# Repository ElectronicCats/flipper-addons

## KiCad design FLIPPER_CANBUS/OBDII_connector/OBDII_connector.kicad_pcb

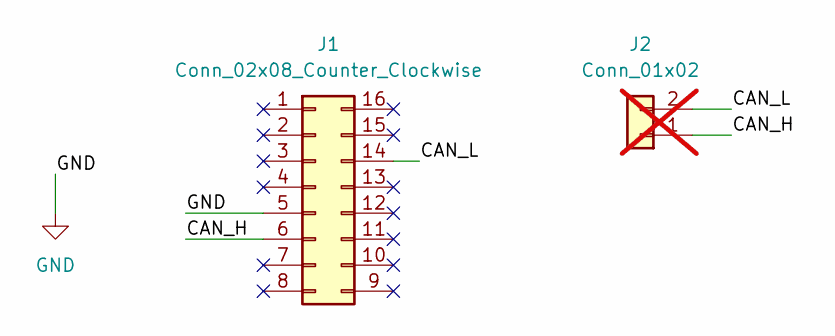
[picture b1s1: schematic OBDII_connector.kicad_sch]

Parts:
J1: Conn_02x08_Counter_Clockwise; OBD-II-Sparkfun v2.0
J2: Conn_01x02; PinHeader_1x02_P2.54mm_Vertical; not fitted

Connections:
/CAN_H: J1.6, J2.1
/CAN_L: J1.14, J2.2
GND: J1.5

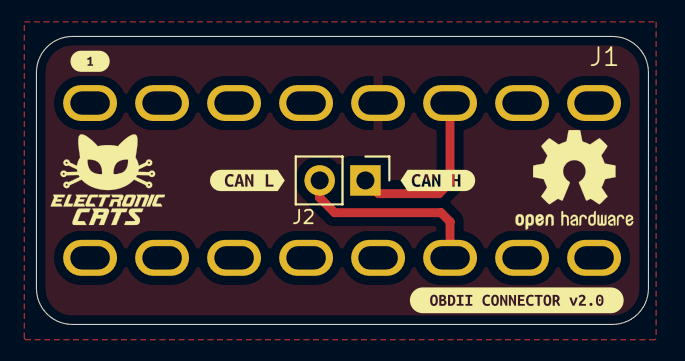
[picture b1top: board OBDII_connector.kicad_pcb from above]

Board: 2 copper layers, 34.0 x 16.0 mm, 6 parts (0 on the bottom side), 2 nets.

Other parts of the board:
kibuzzard-66AA65D6: G***; kibuzzard-66AA65D6
kibuzzard-66AA65F0: G***; kibuzzard-66AA65F0
kibuzzard-6646749E: G***; kibuzzard-6646749E
kibuzzard-66467618: G***; kibuzzard-66467618

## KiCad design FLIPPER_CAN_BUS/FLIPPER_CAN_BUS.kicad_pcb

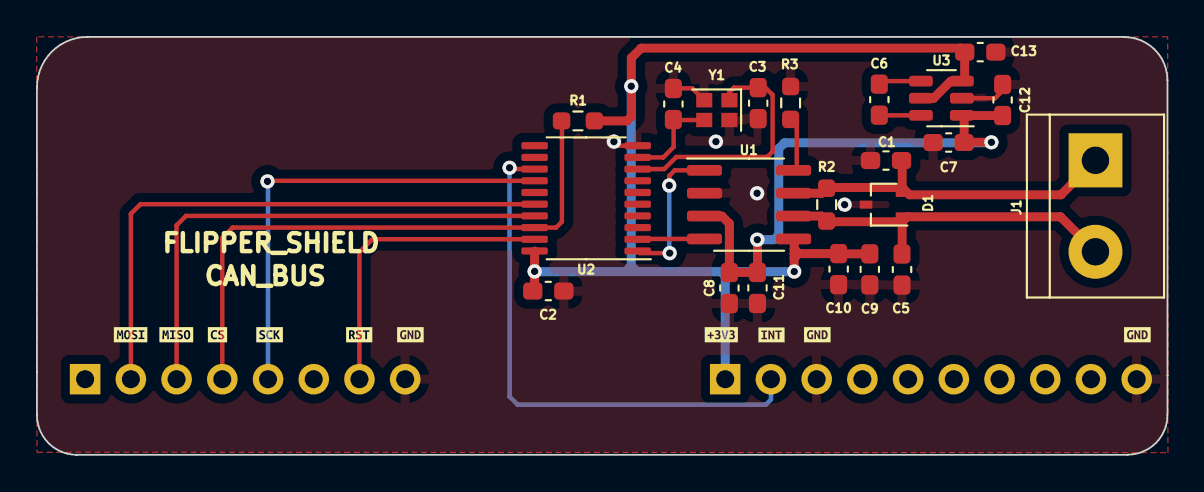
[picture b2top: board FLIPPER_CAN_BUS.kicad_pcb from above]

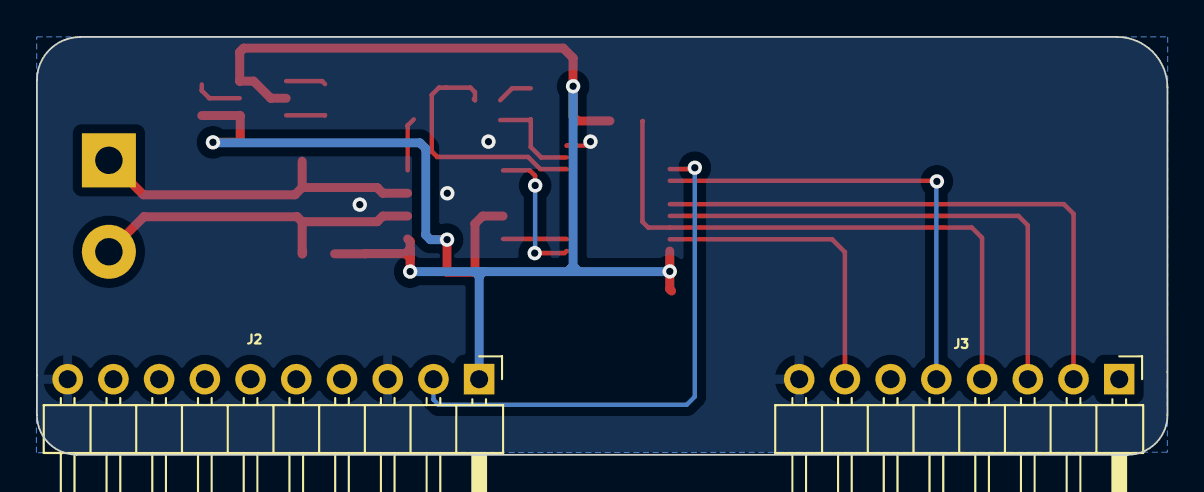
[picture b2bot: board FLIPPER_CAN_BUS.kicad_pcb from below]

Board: 2 copper layers, 62.8 x 23.2 mm, 34 parts (2 on the bottom side), 18 nets.

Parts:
C1, C5: 47pf; C_0603_1608Metric_Pad1.08x0.95mm_HandSolder
C2, C7, C9, C11: 0.1uf; C_0603_1608Metric_Pad1.08x0.95mm_HandSolder
C3, C4: 22pf; C_0603_1608Metric_Pad1.08x0.95mm_HandSolder
C6: 1uf; C_0603_1608Metric_Pad1.08x0.95mm_HandSolder
C8, C10, C12, C13: 10uf; C_0603_1608Metric_Pad1.08x0.95mm_HandSolder
D1: PESD1CAN; SOT-323_SC-70
J1: Conn_01x02; TerminalBlock_bornier-2_P5.08mm
J2: Conn_01x10_Socket; PinHeader_1x10_P2.54mm_Horizontal
J3: Conn_01x08_Socket; PinHeader_1x08_P2.54mm_Horizontal
R1, R3: 10k; R_0603_1608Metric_Pad0.98x0.95mm_HandSolder
R2: 120; R_0603_1608Metric_Pad0.98x0.95mm_HandSolder
U1: TJA1051T/3; SOIC-8_3.9x4.9mm_P1.27mm
U2: MCP2515-xST; TSSOP-20_4.4x6.5mm_P0.65mm
U3: AP3602AKTR-G1; TSOT-23-6
Y1: 16 Mhz; Crystal_SMD_2016-4Pin_2.0x1.6mm
kibuzzard-644AD5B8: G***; kibuzzard-644AD5B8
kibuzzard-644AD5D8: G***; kibuzzard-644AD5D8
kibuzzard-644AD5FD, kibuzzard-644AD5FD#2, kibuzzard-644AD5FD#3: G***; kibuzzard-644AD5FD
kibuzzard-644AD57B: G***; kibuzzard-644AD57B
kibuzzard-644AD570: G***; kibuzzard-644AD570
kibuzzard-644AD586: G***; kibuzzard-644AD586
kibuzzard-644AD591: G***; kibuzzard-644AD591
kibuzzard-644AD616: G***; kibuzzard-644AD616

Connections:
+3V3: C2.2, C9.1, C10.1, C13.1, J2.1, R1.1, U1.5 (VI/O), U2.20 (VDD), U3.3 (*SHDN), U3.5 (VIN)
+5V: C7.1, C8.1, C11.1, C12.1, U1.3 (VCC), U3.1 (VOUT)
/CAN_H: C1.1, D1.2, J1.1, R2.2, U1.7 (CANH)
/CAN_L: C5.2, D1.1, J1.2, R2.1, U1.6 (CANL)
/CS: J3.4, R1.2, U2.18 (~CS)
/INT: J2.2, U2.13 (~INT)
/MISO: J3.3, U2.17 (SO)
/MOSI: J3.2, U2.16 (SI)
/RST: J3.7, U2.19 (~RESET)
/RXD: U1.4 (RXD), U2.2 (RXCAN)
/SCK: J3.5, U2.14 (SCK)
/TXD: U1.1 (TXD), U2.1 (TXCAN)
GND: C1.2, C2.1, C3.1, C4.1, C5.1, C7.2, C8.2, C9.2, C10.2, C11.2, C12.2, C13.2, D1.3, J2.3, J2.10, J3.8, R3.1, U1.2 (GND), U2.10 (VSS), U3.2 (GND), Y1.2, Y1.4
unnamed: R3.2, U1.8 (S)
unnamed: C4.2, U2.9 (OSC1), Y1.3
unnamed: C3.2, U2.8 (OSC2), Y1.1
unnamed: C6.1, U3.6 (C+)
unnamed: C6.2, U3.4 (C-)

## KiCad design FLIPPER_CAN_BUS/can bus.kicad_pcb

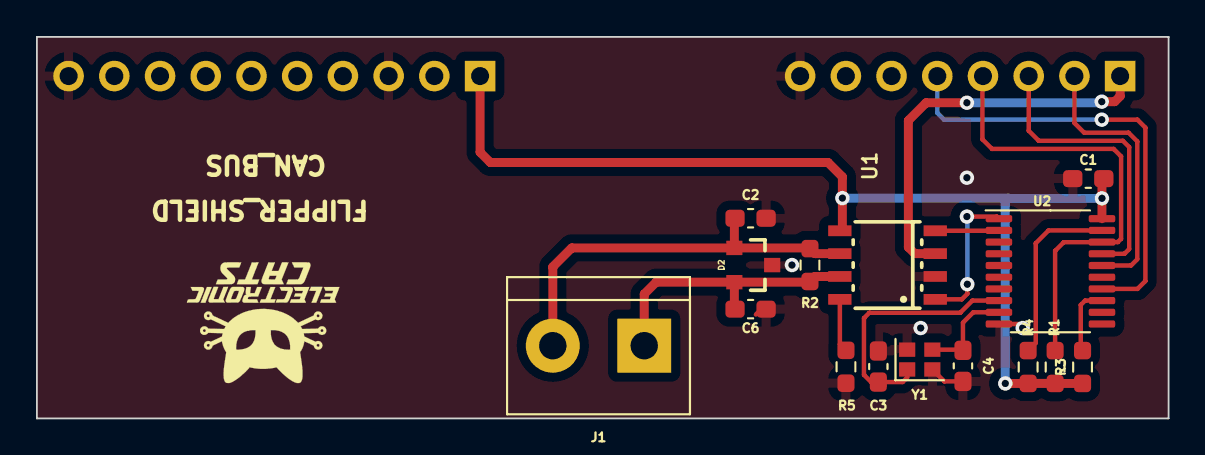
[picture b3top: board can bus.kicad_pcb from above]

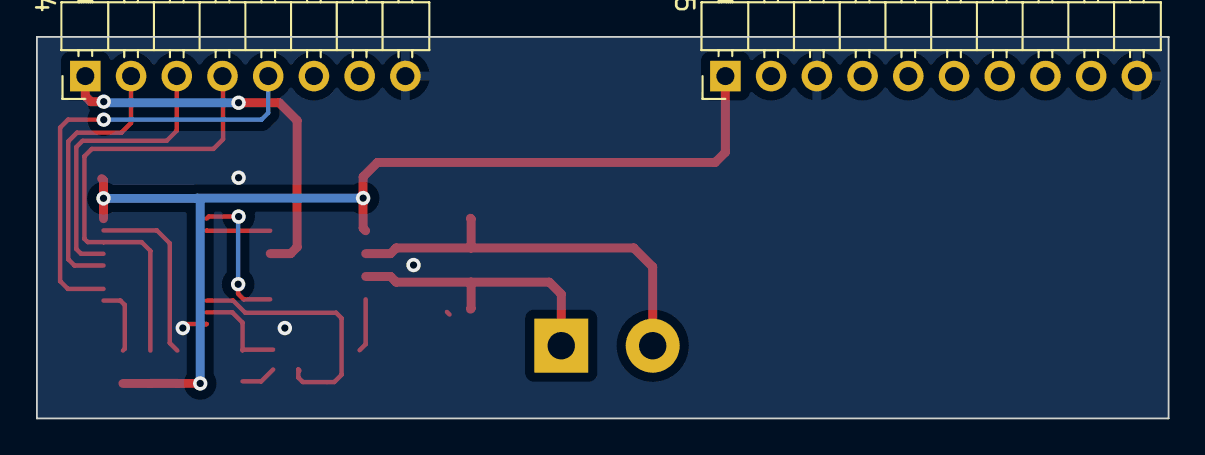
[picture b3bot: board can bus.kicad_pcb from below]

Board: 2 copper layers, 62.9 x 21.2 mm, 17 parts (2 on the bottom side), 16 nets.

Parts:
C1: .1uf; C_0603_1608Metric_Pad1.08x0.95mm_HandSolder
C2, C6: 47pf; C_0603_1608Metric_Pad1.08x0.95mm_HandSolder
C3, C4: 22pf; C_0603_1608Metric_Pad1.08x0.95mm_HandSolder
D2: PESD1CAN; SOT23-3
J1: Conn_01x02; TerminalBlock_bornier-2_P5.08mm
J4: Conn_01x08_Socket; PinHeader_1x08_P2.54mm_Horizontal
J5: Conn_01x10_Socket; PinHeader_1x10_P2.54mm_Horizontal
R1, R3, R4, R5: 10k; R_0603_1608Metric_Pad0.98x0.95mm_HandSolder
R2: 120; R_0603_1608Metric_Pad0.98x0.95mm_HandSolder
U1: TJA1051T/3; SOT96-1
U2: MCP2515-xST; TSSOP-20_4.4x6.5mm_P0.65mm
Y1: 16 Mhz; Crystal_SMD_2016-4Pin_2.0x1.6mm

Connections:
+3V3: C1.1, J5.1, R1.1, R3.1, R4.2, U1.5 (VI/O), U2.20 (VDD)
+5V: J4.1, U1.3 (VCC)
/CAN_H: C6.2, D2.2, J1.1, R2.2, U1.7 (CANH)
/CAN_L: C2.2, D2.1, J1.2, R2.1, U1.6 (CANL)
/CS: J4.4, R1.2, U2.18 (~CS)
/INT: R3.2, U2.13 (~INT)
/MISO: J4.3, U2.17 (SO)
/MOSI: J4.2, U2.16 (SI)
/RST: R4.1, U2.19 (~RESET)
/RXD: U1.4 (RXD), U2.2 (RXCAN)
/SCK: J4.5, U2.14 (SCK)
/TXD: U1.1 (TXD), U2.1 (TXCAN)
GND: C1.2, C2.1, C3.2, C4.2, C6.1, D2.3, J4.8, J5.3, J5.10, R5.1, U1.2 (GND), U2.10 (VSS), Y1.2, Y1.4
unnamed: R5.2, U1.8 (S)
unnamed: C4.1, U2.9 (OSC1), Y1.3
unnamed: C3.1, U2.8 (OSC2), Y1.1

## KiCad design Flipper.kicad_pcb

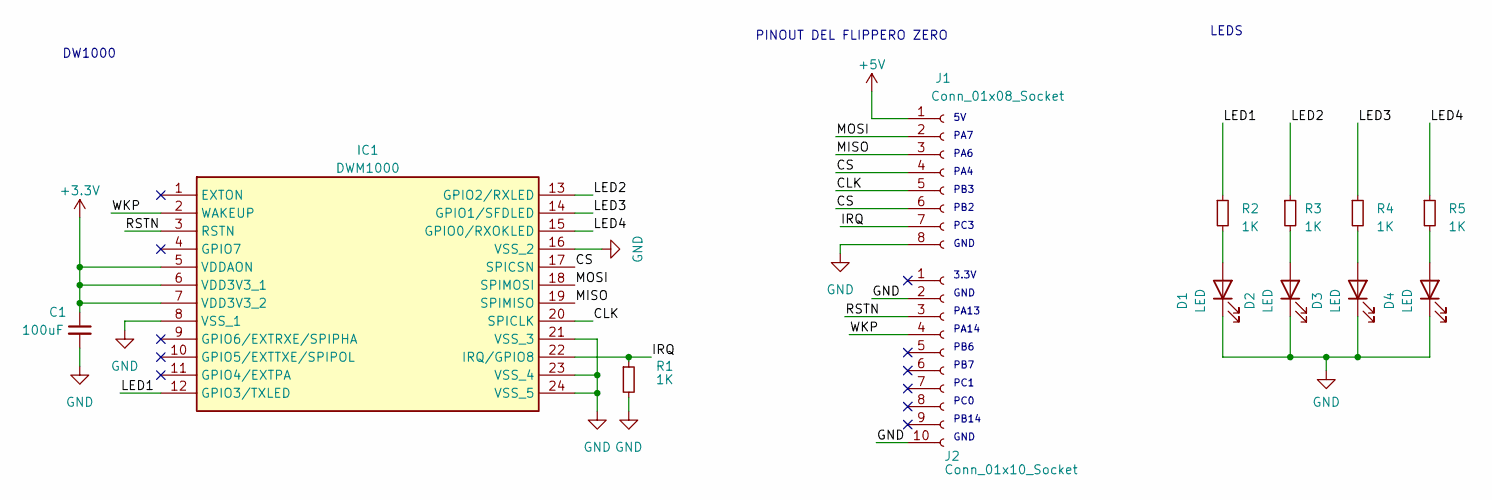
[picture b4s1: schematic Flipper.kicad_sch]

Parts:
C1: 100uF; C_0805_2012Metric
D1, D2, D3, D4: LED; LED_0805_2012Metric
IC1: DWM1000; Mouser Part Number 772-DWM1000
J1: Conn_01x08_Socket; PinHeader_1x08_P2.54mm_Horizontal
J2: Conn_01x10_Socket; PinHeader_1x10_P2.54mm_Horizontal
R1, R2, R3, R4, R5: 1K; R_0805_2012Metric

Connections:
+3.3V: C1.1, IC1.5 (VDDAON), IC1.6 (VDD3V3_1), IC1.7 (VDD3V3_2)
+5V: J1.1
/CLK: IC1.20 (SPICLK), J1.5
/CS: IC1.17 (SPICSN), J1.4, J1.6
/IRQ: IC1.22 (IRQ/GPIO8), J1.7, R1.1
/LED1: IC1.12 (GPIO3/TXLED), R2.1
/LED2: IC1.13 (GPIO2/RXLED), R3.1
/LED3: IC1.14 (GPIO1/SFDLED), R4.1
/LED4: IC1.15 (GPIO0/RXOKLED), R5.1
/MISO: IC1.19 (SPIMISO), J1.3
/MOSI: IC1.18 (SPIMOSI), J1.2
/RSTN: IC1.3 (RSTN), J2.3
/WKP: IC1.2 (WAKEUP), J2.4
GND: C1.2, D1.1 (K), D2.1 (K), D3.1 (K), D4.1 (K), IC1.8 (VSS_1), IC1.16 (VSS_2), IC1.21 (VSS_3), IC1.23 (VSS_4), IC1.24 (VSS_5), J1.8, J2.2, J2.10, R1.2
unnamed: D1.2 (A), R2.2
unnamed: D2.2 (A), R3.2
unnamed: D3.2 (A), R4.2
unnamed: D4.2 (A), R5.2

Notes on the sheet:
PA13
PC1
DW1000
GND
PA6
PA14
PC3
PB3
PB14
PINOUT DEL FLIPPERO ZERO
PB2
PB6
PA7
LEDS
3.3V
PB7
PC0
PA4

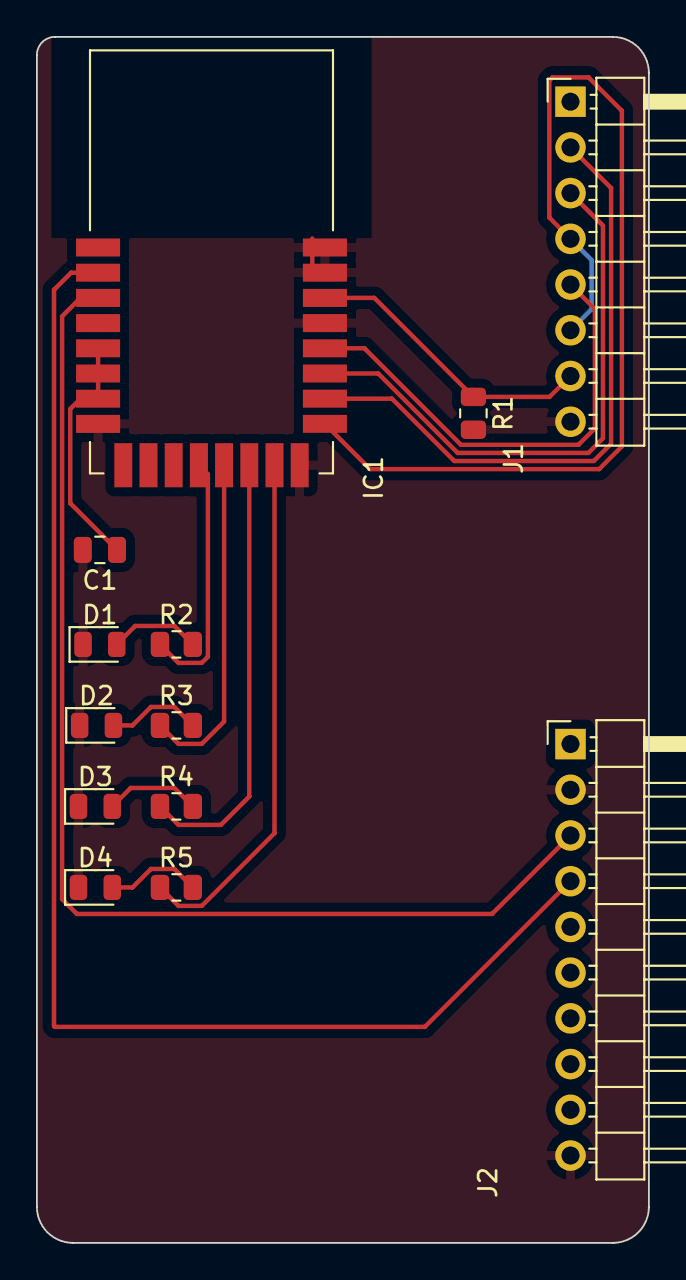
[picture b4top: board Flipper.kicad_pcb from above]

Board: 2 copper layers, 34.0 x 67.0 mm, 13 parts (0 on the bottom side), 17 nets.

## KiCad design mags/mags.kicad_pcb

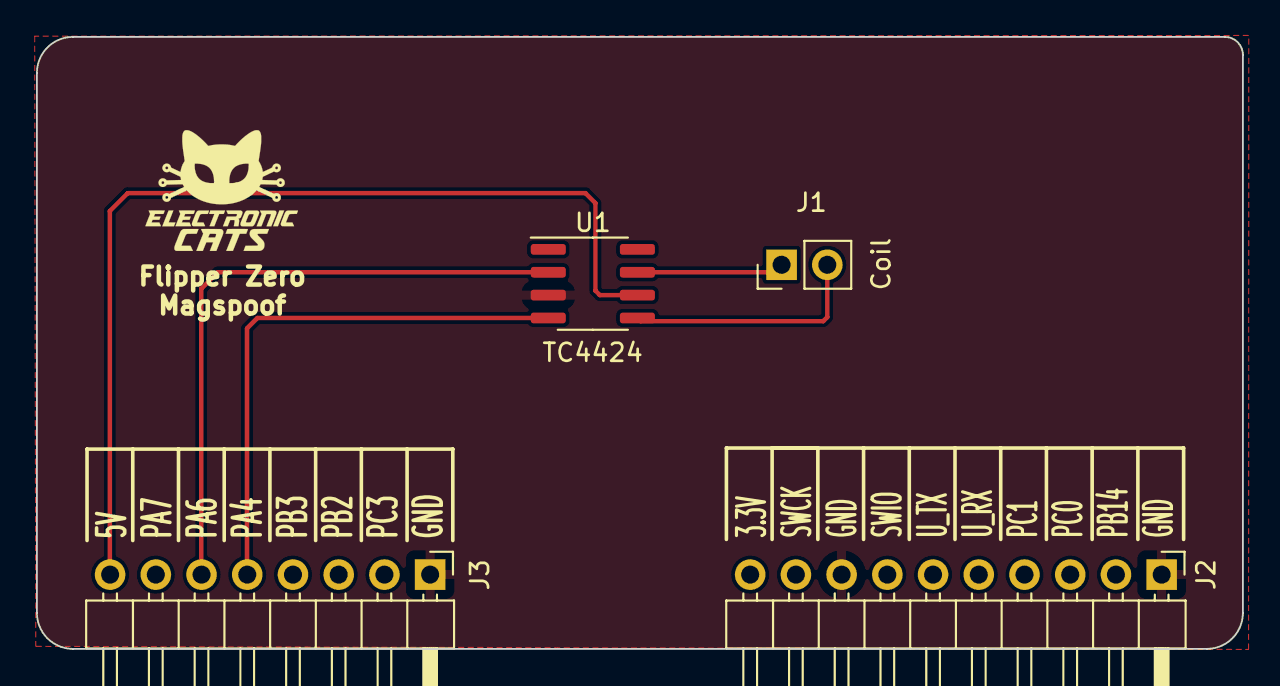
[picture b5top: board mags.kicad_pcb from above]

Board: 2 copper layers, 67.0 x 34.0 mm, 4 parts (0 on the bottom side), 6 nets.

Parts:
J1: Coil; PinHeader_1x02_P2.54mm_Vertical
J2: Conn_01x10_Socket; PinHeader_1x10_P2.54mm_Horizontal
J3: Conn_01x08_Socket; PinHeader_1x08_P2.54mm_Horizontal
U1: TC4424; SOIC-8_3.9x4.9mm_P1.27mm

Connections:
+5V: J3.8 (Pin_1), U1.6 (VDD)
/IN_A: J3.6 (Pin_3), U1.2 (IN_A)
/IN_B: J3.5 (Pin_4), U1.4 (IN_B)
/Out_A: J1.1, U1.7 (OUT_A)
/Out_B: J1.2, U1.5 (OUT_B)
GND: J2.1 (Pin_10), J2.8 (Pin_3), J3.1 (Pin_8), U1.3 (GND)
